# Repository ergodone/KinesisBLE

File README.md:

# Wireless Kinesis Advantage BLE (Bluetooth Low Energy)

Turns the [Kinesis Advantage Keyboard](https://www.kinesis-ergo.com/shop/advantage2/) keyboard into a wireless BLE keyboard with a few extra features. Built with Adafruit's nRF52 Feather Express Arduino boards.

# About this fork

Adds support for the Kinesis Advantage or Professional keyboard to the original KinesisBLE design.  Also makes the PCB slightly smaller which should help minimize cost (specifically for JCLPCB).  The redesign has been done in open-source and free Kicad which should help future development.

# Firmware

The firmware in this repository it not what you want to use.  It's mikewudev's original firmware and is limited compared to ZMK.  

See the [ergodone ZMK repository](https://github.com/ergodone/zmk) for the ZMK firmware. Note there is a more current (and much preferred) ZMK firmware module that supports ZMK studio [ZMK-kinesis repository](https://github.com/ergodone/zmk-kinesis) and builds through GitHub actions (no need to install a build environment). This module is still in actively being worked on (as of 2024-11-08).

# A note on Function Keys

The original function keys are not particularly reliable nor responsive.  A PCB designed to use mechanical switches is documented here: **[Bluelightning32 Function Key Replacement](https://github.com/bluelightning32/kinesis-fn)**  This is not required for the KinesisBLE project but is a worthwhile upgrade if you are doing modifications.

# Wireless Kinesis Advantage BLE (Bluetooth Low Energy)

Turns the [Kinesis Advantage Keyboard](https://www.kinesis-ergo.com/shop/advantage2/) keyboard into a wireless BLE keyboard with a few extra features. Built with Adafruit's nRF52 Feather Express Arduino boards.

For instructions, see the **[wiki](https://github.com/sysdevmike/KinesisBLE/wiki)**. For more details on the build check out the **[project](https://hackaday.io/project/161578-wireless-ble-kinesis-advantage-custom-controller)**.

## Many thanks to

- [Yin Zhong](https://summivox.wordpress.com/2016/06/03/keyboard-matrix-scanning-and-debouncing/) - Explains a better way to handle debouncing.
- [Stapelberg](https://michael.stapelberg.ch/posts/2018-04-17-kinx-keyboard-controller/) - Double mention as I ported his debouncing used in his KinX controller to Matt's firmware.
- [Matt Vilim](https://github.com/mattvilim/FeatherCtrl) - New firmware is a fork of his FeatherCtrl project.
- [Adafruit](https://www.adafruit.com/product/3406) - Great documentation, libs and support.
- [afriggeri](https://github.com/afriggeri/kb) - The original firmware borrowed heavily from his [Blanck Keyboard](https://medium.com/@friggeri/the-blanck-keyboard-24afe12e81a) project.
- [Stapelberg](https://michael.stapelberg.de/posts/2013-03-21-kinesis_custom_controller/) - Michael Stapelberg's custom controller inspired this project. His PCB routing was inspirational.
- [Humble Hacker](http://humblehacker.com/blog/20100720/hacking-the-kinesis-contoured-keyboard/) - Detailed write-up helped me understand the keyboard matrix.
- [PCBgogo](http://www.pcbgogo.com) - All the boards were made by these guys. Fast turn-around.

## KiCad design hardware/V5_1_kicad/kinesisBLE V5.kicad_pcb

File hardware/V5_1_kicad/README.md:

# KinesisBLE with Kinesis Professional/Advantage compatible PCB

These are KiCad files for the KinesisBLE PCB.  The PCB has been made slightly smaller from mikewudev's original design while still maintaining the same connector locations. There is also the option of using the PCB in a Kinesis Professional (with the flex PCB "fingers") by using Molex 39-53-2134 on J2 and J7.  For Kinesis Advantage a Molex 39-53-2135 or Cvilux CF01-13-1V00 is used on J5 and J6.

A couple issues with the layout:
1) the slots for the tabs need to extend 1mm closer to the center of the board.  
2) if you use a jumper for the power button led it may interfere with the usb plug. 
3) the usb cable connector may need to be trimmed down to avoid touching the bottom half of the case (see the image above).

The board has been tested and is currently in use using ZMK firmware.

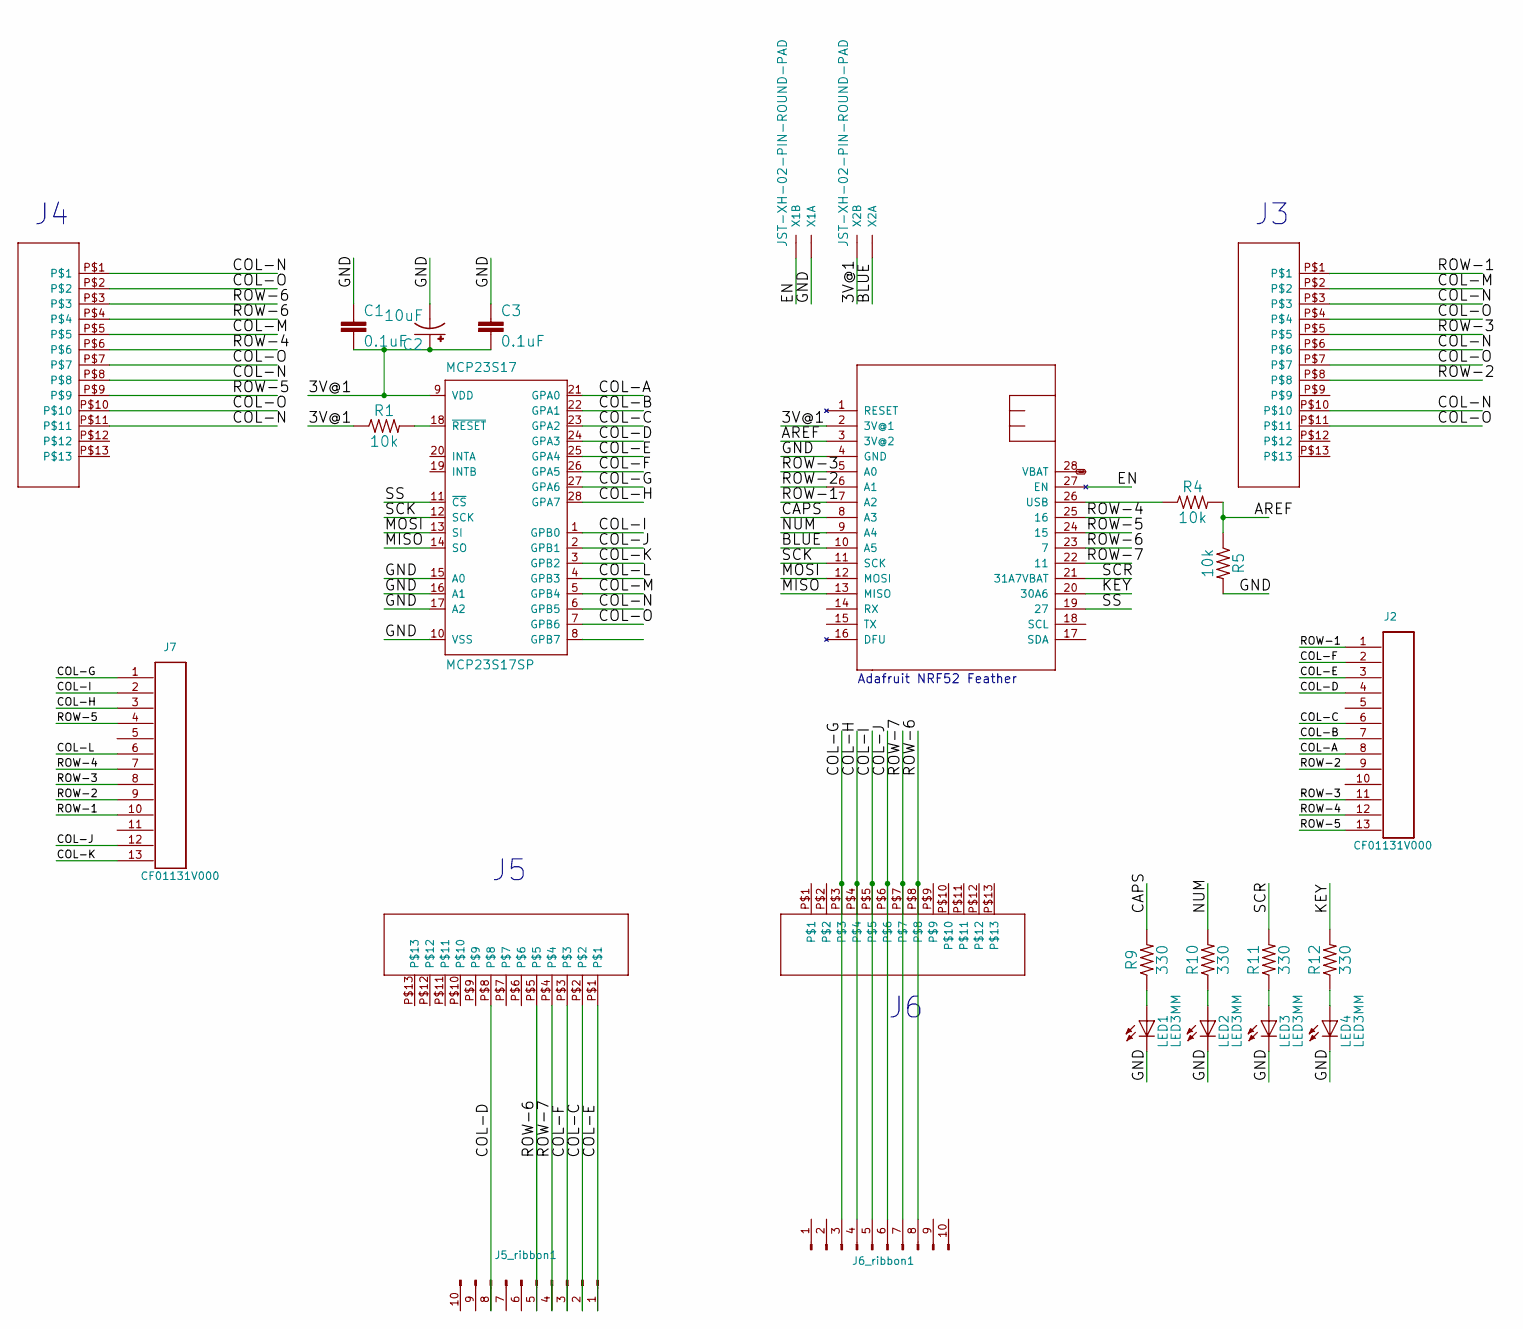
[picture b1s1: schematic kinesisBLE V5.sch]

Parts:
C1, C3: 0.1uF; CAP-PTH-SMALL-KIT
C2: 10uF; CPOL-RADIAL-2.5MM-5MM
J2, J7: CF01131V000; molex 39-53-2134
J5_ribbon1, J6_ribbon1: PinHeader_1x10_P2.54mm; PinHeader_1x10_P2.54mm_Vertical
LED1, LED2, LED3, LED4: LED3MM
MCP23S17: MCP23S17SP; DIL28-3
R1, R4, R5: 10k; AXIAL-0.3
R9, R10, R11, R12: 330; AXIAL-0.3
U$1: NRF52FEATHER
U$2, U$3, U$6, U$7: Cvilux CF01131V000; TOPLINKS_STAPELBERG
X1, X2: JST-XH-02-PIN-ROUND-PAD; JST-XH-02-PACKAGE-ROUND-PAD

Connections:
/3V@1: C1.2, C2.1 (+), C3.2, MCP23S17.9 (VDD), R1.P$1 (1), U$1.2 (3V@1), X2.1
/AREF: R4.P$2 (2), R5.P$1 (1), U$1.3 (3V@2)
/BLUE: U$1.10 (A5), X2.2
/CAPS: R9.P$2 (2), U$1.8 (A3)
/COL-A: J2.8, MCP23S17.21 (GPA0)
/COL-B: J2.7, MCP23S17.22 (GPA1)
/COL-C: J2.6, J5_ribbon1.2, MCP23S17.23 (GPA2), U$6.P$2
/COL-D: J2.4, J5_ribbon1.8, MCP23S17.24 (GPA3), U$6.P$8
/COL-E: J2.3, J5_ribbon1.1, MCP23S17.25 (GPA4), U$6.P$1
/COL-F: J2.2, J5_ribbon1.3, MCP23S17.26 (GPA5), U$6.P$3
/COL-G: J6_ribbon1.3, J7.1, MCP23S17.27 (GPA6), U$7.P$3
/COL-H: J6_ribbon1.4, J7.3, MCP23S17.28 (GPA7), U$7.P$4
/COL-I: J6_ribbon1.5, J7.2, MCP23S17.1 (GPB0), U$7.P$5
/COL-J: J6_ribbon1.6, J7.12, MCP23S17.2 (GPB1), U$7.P$6
/COL-K: J7.13, MCP23S17.3 (GPB2)
/COL-L: J7.6, MCP23S17.4 (GPB3)
/COL-M: MCP23S17.5 (GPB4), U$2.P$5, U$3.P$2
/COL-N: MCP23S17.6 (GPB5), U$2.P$1, U$2.P$8, U$2.P$11, U$3.P$3, U$3.P$6, U$3.P$10
/COL-O: MCP23S17.7 (GPB6), U$2.P$2, U$2.P$7, U$2.P$10, U$3.P$4, U$3.P$7, U$3.P$11
/EN: U$1.27 (EN), X1.1
/GND: C1.1, C2.2 (-), C3.1, LED1.K (C), LED2.K (C), LED3.K (C), LED4.K (C), MCP23S17.10 (VSS), MCP23S17.15 (A0), MCP23S17.16 (A1), MCP23S17.17 (A2), R5.P$2 (2), U$1.4 (GND), X1.2
/KEY: R12.P$2 (2), U$1.20 (30A6)
/MISO: MCP23S17.14 (SO), U$1.13 (MISO)
/MOSI: MCP23S17.13 (SI), U$1.12 (MOSI)
/NUM: R10.P$2 (2), U$1.9 (A4)
/ROW-1: J2.1, J7.10, U$1.7 (A2), U$3.P$1
/ROW-2: J2.9, J7.9, U$1.6 (A1), U$3.P$8
/ROW-3: J2.11, J7.8, U$1.5 (A0), U$3.P$5
/ROW-4: J2.12, J7.7, U$1.25 (16), U$2.P$6
/ROW-5: J2.13, J7.4, U$1.24 (15), U$2.P$9
/ROW-6: J5_ribbon1.5, J6_ribbon1.8, U$1.23 (7), U$2.P$3, U$2.P$4, U$6.P$5, U$7.P$8
/ROW-7: J5_ribbon1.4, J6_ribbon1.7, U$1.22 (11), U$6.P$4, U$7.P$7
/SCK: MCP23S17.12 (SCK), U$1.11 (SCK)
/SCR: R11.P$2 (2), U$1.21 (31A7VBAT)
/SS: MCP23S17.11 (~CS), U$1.19 (27)
unnamed: LED1.A, R9.P$1 (1)
unnamed: LED2.A, R10.P$1 (1)
unnamed: LED3.A, R11.P$1 (1)
unnamed: LED4.A, R12.P$1 (1)
unnamed: MCP23S17.18 (~RESET), R1.P$2 (2)
unnamed: R4.P$1 (1), U$1.26 (USB)
VBAT: U$1.28 (VBAT)

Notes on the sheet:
Adafruit NRF52 Feather

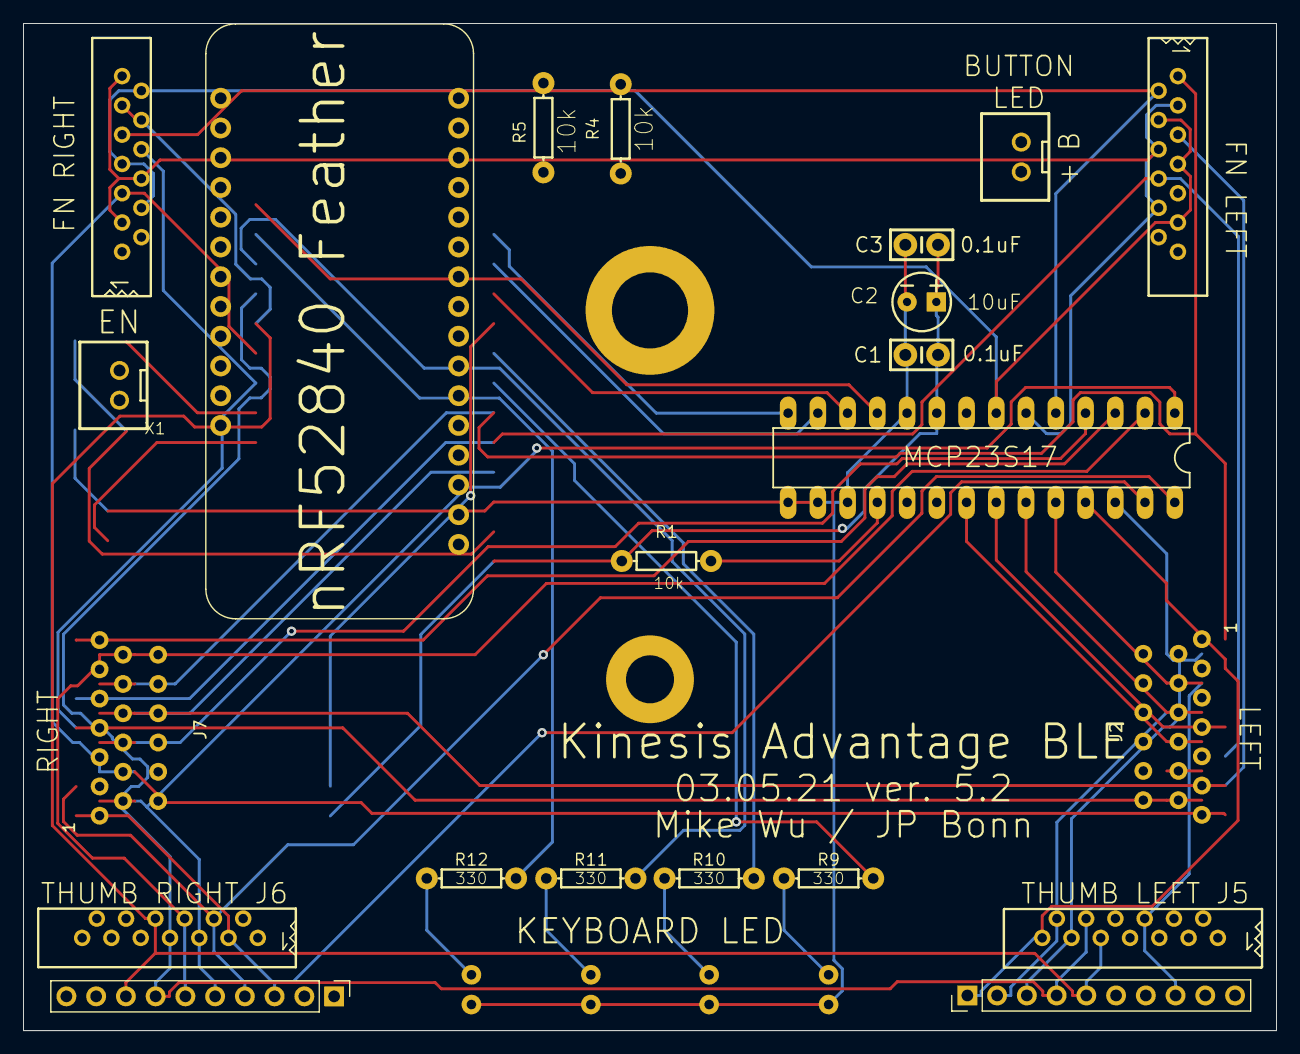
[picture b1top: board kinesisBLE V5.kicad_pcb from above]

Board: 2 copper layers, 107.0 x 86.0 mm, 30 parts (0 on the bottom side), 41 nets.

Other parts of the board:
Hole1: MountingHole_6.5mm_M6_DIN965_Pad; MountingHole_6.4mm_M6_DIN965_Pad
align1, align2: alignment kinesis
hole2: MountingHole_4.3mm_M4_DIN965_Pad

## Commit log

2020-04-27 Kicad/Kinesis Professional version.
2021-02-27 added pictures of board
2021-03-06 corrected physical layout
